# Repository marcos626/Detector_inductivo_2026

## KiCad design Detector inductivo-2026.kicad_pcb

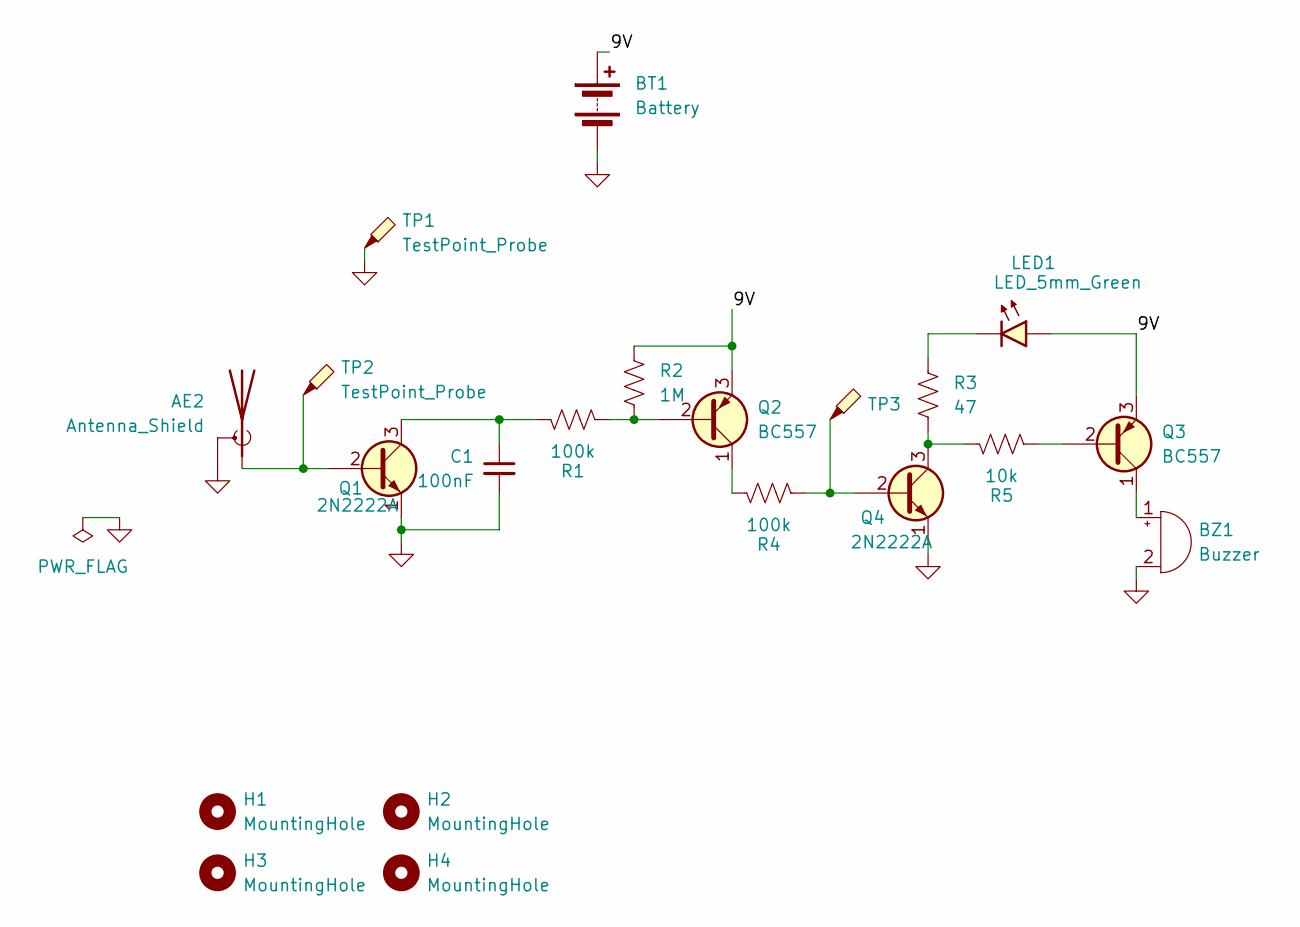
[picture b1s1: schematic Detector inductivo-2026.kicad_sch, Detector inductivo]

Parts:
AE2: Antenna_Shield; SMA_Amphenol_132134-11_Vertical
BT1: Battery; TerminalBlock_Phoenix_MKDS-1,5-2-5.08_1x02_P5.08mm_Horizont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
BZ1: Buzzer; Indicator_PUI_AI-1440-TWT-24V-2-R
C1: 100nF; C_Disc_D4.7mm_W2.5mm_P5.00mm
H1, H2, H3, H4: MountingHole; ToolingHole_1.152mm
LED1: LED_5mm_Green; LED_D5.0mm
Q1, Q4: 2N2222A; TO-92_Inline_Wide_EBC
Q2, Q3: BC557; TO-92_Inline_Wide_CBE
R1, R4: 100k; R_Axial_DIN0207_L6.3mm_D2.5mm_P7.62mm_Horizontal
R2: 1M; R_Axial_DIN0207_L6.3mm_D2.5mm_P7.62mm_Horizontal
R3: 47; R_Axial_DIN0207_L6.3mm_D2.5mm_P7.62mm_Horizontal
R5: 10k; R_Axial_DIN0207_L6.3mm_D2.5mm_P7.62mm_Horizontal
TP1, TP2, TP3: TestPoint_Probe; TestPoint_Bridge_Pitch2.54mm_Drill0.7mm

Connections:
/9V: BT1.1 (+), LED1.2 (A), Q2.3 (E), Q3.3 (E), R2.1
GND: AE2.2 (Shield), BT1.2 (-), BZ1.2 (-), C1.2, Q1.1 (E), Q4.1 (E), TP1.1 (1_1)
unnamed: AE2.1 (A), Q1.2 (B), TP2.1 (1_1)
unnamed: BZ1.1 (+), Q3.1 (C)
unnamed: LED1.1 (K), R3.1
unnamed: C1.1, Q1.3 (C), R1.1
unnamed: Q2.2 (B), R1.2, R2.2
unnamed: Q2.1 (C), R4.1
unnamed: Q3.2 (B), R5.2
unnamed: Q4.2 (B), R4.2, TP3.1 (1_1)
unnamed: Q4.3 (C), R3.2, R5.1

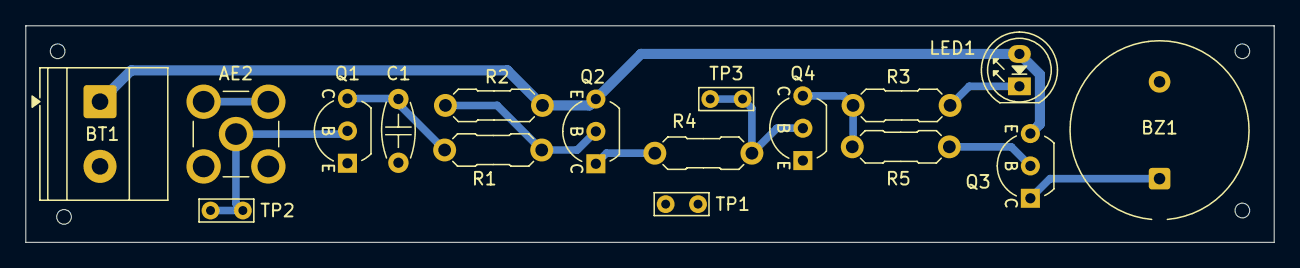
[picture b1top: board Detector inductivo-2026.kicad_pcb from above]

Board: 2 copper layers, 98.0 x 17.0 mm, 21 parts (0 on the bottom side), 11 nets.

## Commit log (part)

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2026-05-17 update board
2026-05-19 cambios en el pcb
2026-05-19 cambios en el terminal de 9V
2026-05-21 ruteo manual
2026-05-26 Hice una matriz de 2x2 y generé el pdf para imprimir
